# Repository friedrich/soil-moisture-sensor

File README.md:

# Moisture sensor

A capacitive moisture sensor board employing an ESP32-C3 RISC-V microcontroller
capable of transmitting measurements via Wi-Fi and Bluetooth 5 (LE). The board
is powered by a single cell LiPo battery, which can be charged using the USB-C
port.

Components are spaced quite far apart, with the goal of making it easier to
solder them by hand.

## Sensor circuit

The sensor circuit consists of the following building blocks:
- The microcontroller generating a square wave, depicted as voltage source
  $U_0$.
- A low pass filter made up of resistor $R_1$ and capacitor $C_1$. Capacitor
  $C_1$ stands for sensor wires together with the medium to be measured acting
  as a dielectric. Its value is to be determined by the circuit.
- A peak voltage detector made up of diode $D_1$, resistor $R_2$ and capacitor
  $C_2$.
- The microcontroller measuring voltage $U_2$.

Since resistor $R_2$ is chosen to be quite large, the impact of the peak voltage
detector on the low pass filter becomes negligible, as soon as $C_2$ reaches a
stable voltage. Just considering the voltage source together with the low pass
filter leads to a peak voltage of

$$ U_p = U_+ \frac{1 - e^{-\omega T D}}{1 - e^{-\omega T}}, $$

where $U_+$ is the high voltage of the voltage source, $T$ the period, $D$ the
duty cycle, and $\omega = 1/(R_1 C_2)$. The peak voltage has a range from $U_+$
for zero $C_2$ down to $D U_+$ for infinite $C_2$.

## Possible future circuit improvements

- Add battery protection circuit.
- Add a switch for turning the device on and off.
- Add a button to put the device into a mode where it acts as an access point or
  can be connected via Bluetooth.
- Make it possible for the microcontroller to measure battery voltage and to
  know if it is powered using USB or the battery. Detect USB using an RTC GPIO
  port to be able to wake the microcontroller when plugged in.
- Replace the battery solder pads with a connector.
- Remove sensing traces from the top so that it matters less how deep the sensor
  is pushed into the soil. Additionally, moisture variations are more relevant
  deeper down than on the top.
- Increase the length of the probe.
- Make it possible to power the board without a battery, using USB-C only. This
  is currently possible by bypassing the battery charge management controller by
  connecting VDD and +BATT. Otherwise, the power supply voltage of the
  microcontroller is not stable.
- Expose JTAG pins for development since the USB-to-JTAG interface is turned off
  during deep sleep.

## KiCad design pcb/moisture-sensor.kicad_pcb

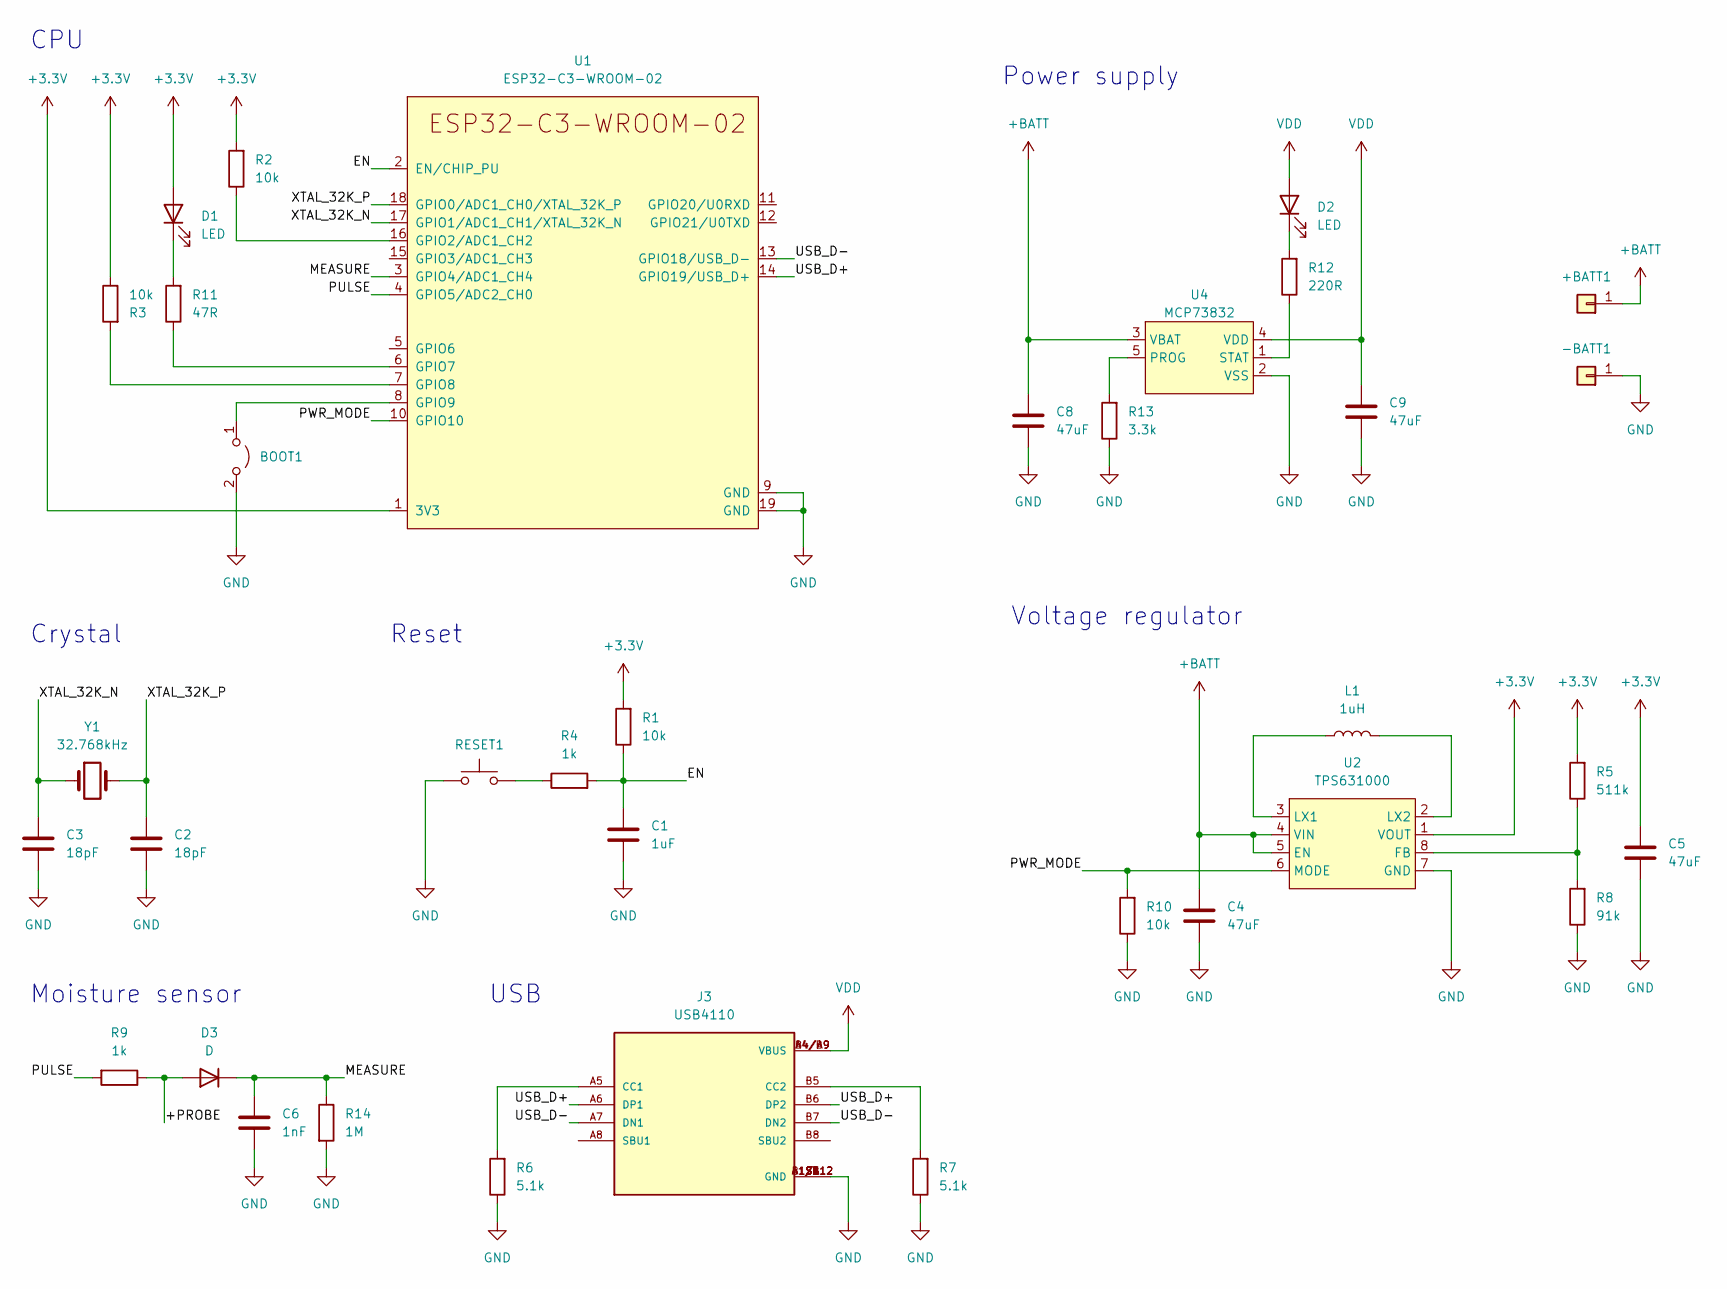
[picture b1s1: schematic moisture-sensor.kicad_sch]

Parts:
+BATT1: Conn_01x01; SolderWire-0.25sqmm_1x01_D0.65mm_OD1.7mm
-BATT1: Conn_01x01; SolderWire-0.25sqmm_1x01_D0.65mm_OD1.7mm
BOOT1: Jumper_2_Open; SolderJumper-2_P1.3mm_Open_RoundedPad1.0x1.5mm
C1: 1uF; C_0805_2012Metric_Pad1.18x1.45mm_HandSolder; MPN GRM219R7YA105KA12
C2, C3: 18pF; C_0805_2012Metric_Pad1.18x1.45mm_HandSolder; MPN GRM21A5C2E180JW01
C4, C5, C8, C9: 47uF; C_0805_2012Metric_Pad1.18x1.45mm_HandSolder; MPN GRM21BR61A476ME15
C6: 1nF; C_0805_2012Metric_Pad1.18x1.45mm_HandSolder; MPN GRM2165C2A102JA01
D1, D2: LED; D_0805_2012Metric_Pad1.15x1.40mm_HandSolder; MPN LTST-C170KGKT
D3: D; D_SOD-323_HandSoldering; MPN BAV16WS-7-F
J3: USB4110; USB4110-GF-A_REVB; MPN USB4110-GF-A
L1: 1uH; L_1008_2520Metric_Pad1.43x2.20mm_HandSolder; MPN DFE252012P-1R0M=P2
R1, R2, R3, R10: 10k; R_0805_2012Metric_Pad1.20x1.40mm_HandSolder; MPN RC0805FR-0710KL
R4, R9: 1k; R_0805_2012Metric_Pad1.20x1.40mm_HandSolder; MPN RC0805FR-071KL
R5: 511k; R_0805_2012Metric_Pad1.20x1.40mm_HandSolder; MPN RC0805FR-07511KL
R6, R7: 5.1k; R_0805_2012Metric_Pad1.20x1.40mm_HandSolder; MPN RC0805FR-075K1L
R8: 91k; R_0805_2012Metric_Pad1.20x1.40mm_HandSolder; MPN RC0805FR-0791KL
R11: 47R; R_0805_2012Metric_Pad1.20x1.40mm_HandSolder; MPN RC0805FR-0747RL
R12: 220R; R_0805_2012Metric_Pad1.20x1.40mm_HandSolder; MPN RC0805FR-07220RL
R13: 3.3k; R_0805_2012Metric_Pad1.20x1.40mm_HandSolder; MPN RC0805FR-073K3L
R14: 1M; R_0805_2012Metric_Pad1.20x1.40mm_HandSolder; MPN RC0805FR-071ML
RESET1: EVQ-Q2F03W; SW_SPST_EVQP2; MPN EVQ-P2K02Q
U1: ESP32-C3-WROOM-02; MPN ESP32-C3-WROOM-02-N4
U2: TPS631000; SC-70-8; MPN TPS631000DRLR
U4: MCP73832; SOT-23-5_HandSoldering; MPN MCP73832T-2DCI/OT
Y1: 32.768kHz; Crystal_SMD_G8-2Pin_3.2x1.5mm_HandSoldering; MPN ABS07-32.768KHZ-T

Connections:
+3.3V: C5.1, D1.2 (A), R1.2, R2.2, R3.1, R5.2, U1.1 (3V3), U2.1 (VOUT)
+BATT: +BATT1.1, C4.1, C8.2, U2.4 (VIN), U2.5 (EN), U4.3 (VBAT)
/+PROBE: D3.2 (A), R9.1
/EN: C1.2, R1.1, R4.2, U1.2 (EN/CHIP_PU)
/MEASURE: C6.1, D3.1 (K), R14.1, U1.3 (GPIO4/ADC1_CH4)
/PULSE: R9.2, U1.4 (GPIO5/ADC2_CH0)
/PWR_MODE: R10.2, U1.10 (GPIO10), U2.6 (MODE)
/USB_D+: J3.A6 (DP1), J3.B6 (DP2), U1.14 (GPIO19/USB_D+)
/USB_D-: J3.A7 (DN1), J3.B7 (DN2), U1.13 (GPIO18/USB_D-)
/XTAL_32K_N: C3.2, U1.17 (GPIO1/ADC1_CH1/XTAL_32K_N), Y1.1
/XTAL_32K_P: C2.2, U1.18 (GPIO0/ADC1_CH0/XTAL_32K_P), Y1.2
GND: -BATT1.1, BOOT1.2 (B), C1.1, C2.1, C3.1, C4.2, C5.2, C6.2, C8.1, C9.1, J3.A1/B12 (GND), J3.B1/A12 (GND), J3.S1 (GND), J3.S2 (GND), J3.S3 (GND), J3.S4 (GND), R6.1, R7.1, R8.1, R10.1, R13.1, R14.2, RESET1.1, U1.9 (GND), U1.19 (GND), U2.7 (GND), U4.2 (VSS)
unnamed: BOOT1.1 (A), U1.8 (GPIO9)
unnamed: D1.1 (K), R11.2
unnamed: D2.1 (K), R12.2
unnamed: J3.A5 (CC1), R6.2
unnamed: J3.B5 (CC2), R7.2
unnamed: L1.1, U2.3 (LX1)
unnamed: L1.2, U2.2 (LX2)
unnamed: R2.1, U1.16 (GPIO2/ADC1_CH2)
unnamed: R3.2, U1.7 (GPIO8)
unnamed: R4.1, RESET1.2
unnamed: R5.1, R8.2, U2.8 (FB)
unnamed: R11.1, U1.6 (GPIO7)
unnamed: R12.1, U4.1 (STAT)
unnamed: R13.2, U4.5 (PROG)
VDD: C9.2, D2.2 (A), J3.A4/B9 (VBUS), J3.B4/A9 (VBUS), U4.4 (VDD)

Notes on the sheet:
Power supply
Crystal
Moisture sensor
Voltage regulator
CPU
Reset
USB

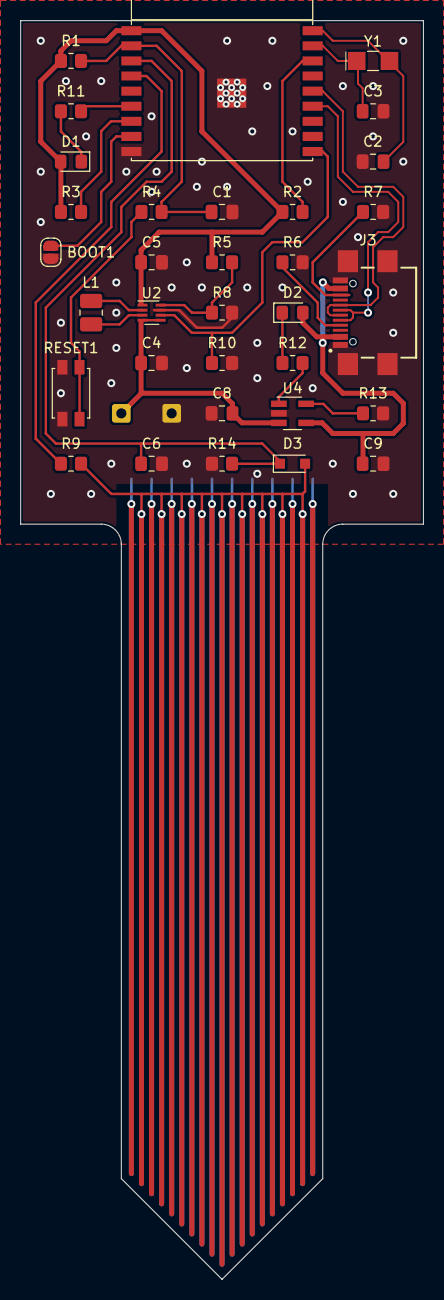
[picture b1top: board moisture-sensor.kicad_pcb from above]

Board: 2 copper layers, 40.0 x 125.0 mm, 35 parts (0 on the bottom side), 27 nets.

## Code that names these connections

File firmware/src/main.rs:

mod arr_deque;

use crate::arr_deque::ArrDeque;
use anyhow::{anyhow, bail, Context, Result};
use chrono::Utc;
use embedded_svc;
use embedded_svc::http::Method;
use embedded_svc::io::Write;
use esp_idf_hal::units::FromValueType;
use esp_idf_hal::{adc, gpio, ledc, reset};
use esp_idf_hal::{delay::FreeRtos, peripherals};
use esp_idf_svc::netif::IpEvent;
use esp_idf_svc::wifi::{EspWifi, WifiEvent};
use esp_idf_svc::{eventloop, nvs, sntp};
use std::sync::mpsc::channel;
use std::time::Duration;

const WIFI_SSID: &str = env!("WIFI_SSID");
const WIFI_PASSWORD: &str = env!("WIFI_PASSWORD");

const WRITE_URL: &str = env!("WRITE_URL");
const AUTHORIZATION: &str = env!("AUTHORIZATION");
const LINE_PREFIX: &str = env!("LINE_PREFIX");

const MEASUREMENT_INTERVAL: Duration = Duration::from_secs(3600);
const MIN_RECORDED_MEASUREMENTS: usize = 6;
const MAX_RECORDED_MEASUREMENTS: usize = 1000;

#[derive(Clone)]
struct Measurement {
    value: u16,
    battery_voltage: u16,
    time: u32,
}

#[link_section = ".rtc.data.rtc_memory"]
static mut MEASUREMENTS: ArrDeque<Measurement, MAX_RECORDED_MEASUREMENTS> = ArrDeque::new();

fn main() -> Result<()> {
    esp_idf_sys::link_patches();

    if let Err(e) = run() {
        println!("error: {}", e);
    }

    unsafe {
        go_to_sleep();
    }
}

fn run() -> Result<()> {
    let peripherals = peripherals::Peripherals::take().context("peripherals already taken")?;
    let mut led_driver = gpio::PinDriver::output(peripherals.pins.gpio7)?;

    let mut power_mode_driver = gpio::PinDriver::output(peripherals.pins.gpio10)?;
    power_mode_driver.set_high()?;

    let mut adc_driver = adc::AdcDriver::new(
        peripherals.adc1,
        &adc::config::Config::new().calibration(true),
    )?;
    let mut adc_channel_driver: adc::AdcChannelDriver<gpio::Gpio4, adc::Atten11dB<_>> =
        adc::AdcChannelDriver::new(peripherals.pins.gpio4)?;

    let mut battery_adc_channel_driver: adc::AdcChannelDriver<gpio::Gpio3, adc::Atten11dB<_>> =
        adc::AdcChannelDriver::new(peripherals.pins.gpio3)?;

    let pwm_config = ledc::config::TimerConfig::new().frequency(50.kHz().into());
    let mut sensor_pwm_driver = ledc::LedcDriver::new(
        peripherals.ledc.channel0,
        ledc::LedcTimerDriver::new(peripherals.ledc.timer0, &pwm_config)?,
        peripherals.pins.gpio5,
        &pwm_config,
    )?;

    let clock_source = unsafe { esp_idf_sys::rtc_clk_slow_freq_get() };
    if clock_source != esp_idf_sys::rtc_slow_freq_t_RTC_SLOW_FREQ_32K_XTAL {
        bail!("wrong slow clock source");
    }

    if reset::ResetReason::get() != reset::ResetReason::DeepSleep {
        greeting(&mut led_driver)?;
    } else {
        led_driver.set_high()?;
    }

    sensor_pwm_driver.set_duty(sensor_pwm_driver.get_max_duty() / 100)?;
    FreeRtos::delay_ms(20); // TODO: good value?

    let battery_voltage = adc_driver.read(&mut battery_adc_channel_driver)?;

    match adc_driver.read(&mut adc_channel_driver) {
        Ok(value) => {
            let time = slow_clock_seconds();
            println!("recorded value: {} at {}", value, time);

            unsafe {
                MEASUREMENTS.overwriting_push_back(Measurement {
                    value,
                    battery_voltage,
                    time,
                });
                if MEASUREMENTS.len() < MIN_RECORDED_MEASUREMENTS {
                    return Ok(());
                }
            }
        }
        Err(e) => {
            bail!("error measuring: {}", e);
        }
    };

    let sysloop = eventloop::EspSystemEventLoop::take()?;
    let nvs_partition = nvs::EspDefaultNvsPartition::take()?;

    let mut esp_wifi = EspWifi::new(peripherals.modem, sysloop.clone(), Some(nvs_partition))?;
    esp_wifi.set_configuration(&embedded_svc::wifi::Configuration::Client(
        embedded_svc::wifi::ClientConfiguration {
            ssid: WIFI_SSID.into(),
            password: WIFI_PASSWORD.into(),
            channel: None,
            ..Default::default()
        },
    ))?;

    let (wifi_started_tx, wifi_started_rx) = channel();
    let (wifi_connected_tx, wifi_connected_rx) = channel();
    let _wifi_subscription = sysloop.subscribe(move |event: &WifiEvent| match event {
        WifiEvent::StaStarted => {
            let _ = wifi_started_tx.send(());
        }
        WifiEvent::StaConnected => {
            let _ = wifi_connected_tx.send(Ok(()));
        }
        WifiEvent::StaDisconnected => {
            let _ = wifi_connected_tx.send(Err(anyhow!("WiFi disconnected")));
        }
        _ => {}
    })?;

    let (ip_assigned_tx, ip_assigned_rx) = channel();
    let _netif_subscription = sysloop.subscribe(move |event: &IpEvent| match event {
        IpEvent::DhcpIpAssigned(_) | IpEvent::DhcpIp6Assigned(_) => {
            let _ = ip_assigned_tx.send(());
        }
        _ => {}
    })?;

    esp_wifi.start()?;

    wifi_started_rx.recv()?;
    println!("connecting WiFi...");
    esp_wifi.connect()?;

    wifi_connected_rx.recv()??;
    println!("WiFi connected.");

    ip_assigned_rx.recv()?;
    println!("IP address obtained, syncing time....");

    let sntp = sntp::EspSntp::new_default()?;
    while sntp.get_sync_status() != sntp::SyncStatus::Completed {
        FreeRtos::delay_ms(100);
    }
    println!("time synced, sending data..");

    let time_offset = Utc::now().timestamp() - slow_clock_seconds() as i64;

    let measurements: Vec<_> = unsafe { MEASUREMENTS.iter().cloned().collect() };
    send_values(measurements.as_slice(), time_offset)?;
    println!("successfully sent data.");

    unsafe {
        MEASUREMENTS = ArrDeque::new();
    }

    Ok(())
}

fn slow_clock_seconds() -> u32 {
    let rtc_time = unsafe { esp_idf_sys::rtc_time_get() };
    (rtc_time / u64::from(esp_idf_sys::RTC_SLOW_CLK_FREQ_32K)) as _
}

fn greeting<T: gpio::Pin, MODE: gpio::OutputMode>(
    led_pin: &mut gpio::PinDriver<T, MODE>,
) -> Result<()> {
    for _ in 0..4 {
        led_pin.set_low()?;
        FreeRtos::delay_ms(20);
        led_pin.set_high()?;
        FreeRtos::delay_ms(100);
    }
    FreeRtos::delay_ms(400);
    led_pin.set_low()?;
    FreeRtos::delay_ms(1000);
    led_pin.set_high()?;
    FreeRtos::delay_ms(500);

    Ok(())
}

unsafe fn go_to_sleep() -> ! {
    let delay = MEASUREMENT_INTERVAL.as_micros() as _;
    esp_idf_sys::esp_sleep_enable_timer_wakeup(delay);
    esp_idf_sys::esp_deep_sleep_start();
    unreachable!();
}

fn send_values(measurements: &[Measurement], time_offset: i64) -> anyhow::Result<()> {
    let http_client_config = esp_idf_svc::http::client::Configuration {
        crt_bundle_attach: Some(esp_idf_sys::esp_crt_bundle_attach),
        ..Default::default()
    };

    let data: String = measurements
        .iter()
        .map(|m| {
            format!(
                "{}{},battery_voltage={} {}000000000\n",
                LINE_PREFIX,
                m.value,
                m.battery_voltage,
                m.time as i64 + time_offset
            )
        })
        .collect();

    println!("{}", data);

    let content_length = data.len().to_string();
    let headers = vec![
        ("Authorization", AUTHORIZATION),
        ("Content-Length", &content_length),
    ];

    let mut http_client = esp_idf_svc::http::client::EspHttpConnection::new(&http_client_config)?;
    http_client.initiate_request(Method::Post, WRITE_URL, &headers)?;
    http_client.write_all(data.as_bytes())?;
    http_client.initiate_response()?;

    let status = http_client.status();
    if status < 200 || status >= 300 {
        let mut response = vec![0; 1000];
        http_client.read(&mut response)?;
        bail!(
            "HTTP status {}: {}",
            status,
            String::from_utf8_lossy(&response)
        );
    }

    Ok(())
}

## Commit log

2022-11-08 create first PCB version
2022-11-08 improve PCB
2022-11-08 add rendering
2022-11-09 add footprints and 3d models, increase solder pad size
2022-11-09 adjust some component values
2022-11-09 ignore generated file
2022-11-20 extend README
2022-11-20 add battery text
2022-11-20 fix reset button
2022-11-20 clarify sensor circuit
2022-11-21 add datasheet to schematic
2022-11-21 add list of possible future improvements
2022-11-21 update KiCad file version
2022-11-21 add schematic as PDF
2022-11-21 prefer built in KiCad items
2022-11-22 add more future improvements
2022-11-24 add firmware
2022-11-25 add future improvements
2022-11-26 add note about peak voltage range
2022-11-26 change symbol for duty cycle
2022-11-26 increase power supply capacitor sizes
2022-11-27 Revert "increase power supply capacitor sizes"
    This reverts commit e628d20ff7827fca777ef456cf9c7b65b2cb21d5.
2022-11-27 add note about power supply
2022-11-27 store measurements in memory before sending them in batches
2022-11-28 use external crystal
2022-11-28 remove unnecessary delay
2022-11-28 check clock source on start
2022-11-28 print recorded value
2022-11-28 add future improvement
2022-11-28 add license
2022-12-03 reduce measurement interval
2022-12-05 add battery voltage measurement
